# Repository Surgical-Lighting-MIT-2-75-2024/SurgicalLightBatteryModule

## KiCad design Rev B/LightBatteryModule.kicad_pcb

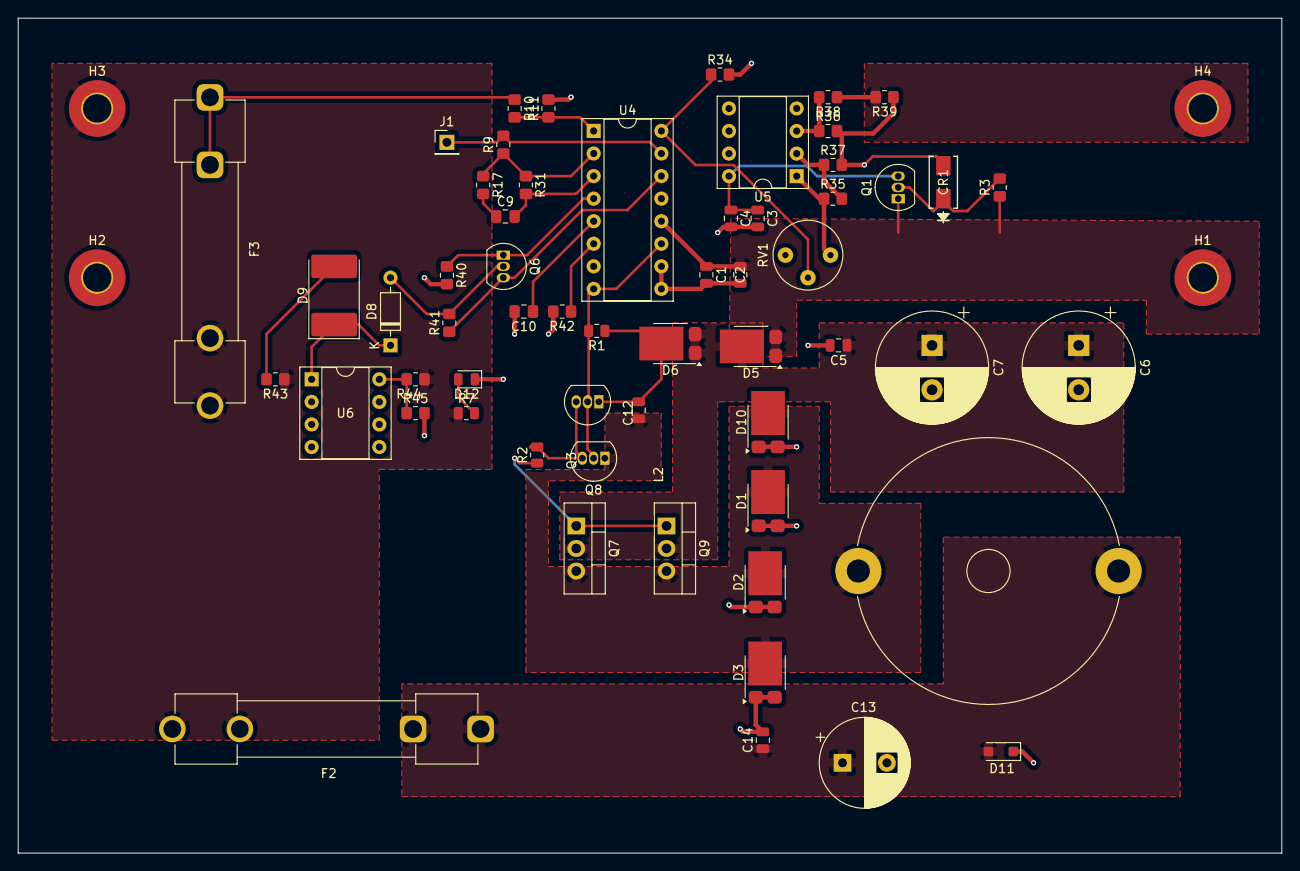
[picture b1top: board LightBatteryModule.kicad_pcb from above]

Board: 2 copper layers, 142.2 x 94.0 mm, 62 parts (0 on the bottom side), 32 nets.

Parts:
C1, C3: 1uF; C_0805_2012Metric
C2, C4, C5, C12, C14: 0.1uF; C_0805_2012Metric
C6, C7: 470uF; CP_Radial_D12.5mm_P5.00mm
C9: 100nF; C_0805_2012Metric_Pad1.18x1.45mm_HandSolder
C10: 1nF; C_0805_2012Metric_Pad1.18x1.45mm_HandSolder
C13: 22uF; CP_Radial_D10.0mm_P5.00mm
CR1: SMAZ15-13-F; SMA_DIO
D1, D2, D3, D5, D6, D10: PMEG045V150EPD; Nexperia_CFP15_SOT-1289
D8: 1N4148; D_DO-35_SOD27_P7.62mm_Horizontal
D9: LED; D_3220_8050Metric_Pad2.65x5.15mm_HandSolder
D11: SZSMF4L15CAT3G; D_SOD-123F
D12: LED Green; LED_0805_2012Metric
F2, F3: 12A; Fuseholder_Clip-6.3x32mm_Littelfuse_102071_Inline_P34.70x7.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
H1, H2, H3, H4: M3 Hole; MountingHole_3.2mm_M3_Pad_TopBottom
J1: Conn_01x01_Pin; PinHeader_1x01_P2.54mm_Vertical
L2: 100uH 10.5A; L_Radial_D29.8mm_P29.30mm_Murata_1400series
Q1: 2n3904; TO-92_Inline
Q3: BC337; TO-92_Inline
Q6: BC557; TO-92_Inline
Q7, Q9: IRLZ44N; TO-220-3_Vertical
Q8: BC327; TO-92_Inline
R1: 2k2; R_0805_2012Metric
R2: 5; R_0805_2012Metric
R3, R10, R41, R44: 10K; R_0805_2012Metric_Pad1.20x1.40mm_HandSolder
R7: 1K; R_0805_2012Metric
R9: 1K; R_0805_2012Metric_Pad1.20x1.40mm_HandSolder
R11: 2.2K; R_0805_2012Metric_Pad1.20x1.40mm_HandSolder
R17, R35, R36: 47K; R_0805_2012Metric_Pad1.20x1.40mm_HandSolder
R31: 56k; R_0805_2012Metric_Pad1.20x1.40mm_HandSolder
R34: 560R; R_0805_2012Metric_Pad1.20x1.40mm_HandSolder
R37, R38, R45: 2K; R_0805_2012Metric_Pad1.20x1.40mm_HandSolder
R39: 0R1; R_0805_2012Metric_Pad1.20x1.40mm_HandSolder
R40, R43: 2K2; R_0805_2012Metric_Pad1.20x1.40mm_HandSolder
R42: 39K; R_0805_2012Metric_Pad1.20x1.40mm_HandSolder
RV1: 10K; Potentiometer_Bourns_3339P_Vertical_HandSoldering
U4: TL494; DIP-16_W7.62mm_Socket
U5: LM358; DIP-8_W7.62mm_Socket
U6: TL431D; DIP-8_W7.62mm_Socket

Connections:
/CT: C10.1, U4.5 (CT)
/EA1+: R10.2, R11.1, U4.1 (1IN+)
/EA1-: R9.1, R17.1, R31.1, U4.2 (1IN-)
/EA2+: R34.1, RV1.2, U4.16 (2IN+)
/FB: C9.2, R31.2, U4.3 (FB)
/PWM Out: Q3.2 (B), Q8.2 (B), R1.2, U4.8 (C1), U4.11 (C2)
/RT: R42.1, U4.6 (RT)
/SOLAR 15V: C3.1, C4.1, Q1.3 (E), U5.8 (V+)
/VPOut: Q6.1 (C), R40.1, U4.4 (DTC)
/VREF: Q6.3 (E), R41.1, U4.14 (REF)
BAT+: F2.2, F3.2, H3.1, R7.1, R43.1, R44.1
BAT-: H4.1, R38.1, R39.2
GND: C1.2, C2.2, C3.2, C4.2, C5.2, C6.2, C7.2, C10.2, C13.2, C14.2, CR1.2, D1.1 (A), D1.2 (A), D2.1 (A), D2.2 (A), D3.1 (A), D3.2 (A), D10.1 (A), D10.2 (A), D11.1 (A1), D12.1 (K), H2.1, R11.2, R34.2, R36.2, R37.2, R39.1, R40.2, R42.2, R45.2, U4.7 (GND), U4.9 (E1), U4.10 (E2), U4.13 (OUTCTRL), U5.4 (V-), U6.2 (A), U6.3 (A), U6.6 (A), U6.7 (A)
MCU 2.5V: J1.1, R9.2, U4.15 (2IN-)
unnamed: C9.1, R17.2
unnamed: C12.2, D1.3 (K), D2.3 (K), D3.3 (K), D10.3 (K), L2.1, Q7.3 (S), Q8.1 (C), Q9.3 (S)
unnamed: C5.1, C6.1, C7.1, D5.3 (K), D6.1 (A), D6.2 (A), Q7.2 (D), Q9.2 (D)
unnamed: C12.1, D6.3 (K), Q3.1 (C), R1.1
unnamed: D8.2 (A), Q6.2 (B), R41.2
unnamed: D8.1 (K), D9.1 (K), U6.1 (K)
unnamed: D9.2 (A), R43.2
unnamed: C13.1, C14.1, D11.2 (A2), F2.1, L2.2
unnamed: D12.2 (A), R7.2
unnamed: F3.1, R10.1
unnamed: CR1.1, Q1.2 (B), R3.2
unnamed: Q3.3 (E), Q8.3 (E), R2.2
unnamed: Q7.1 (G), Q9.1 (G), R2.1
unnamed: R35.1, RV1.1, U5.1
unnamed: R36.1, R38.2, U5.3 (+)
unnamed: R35.2, R37.1, U5.2 (-)
unnamed: R44.2, R45.1, U6.8 (REF)
SOLAR+: C1.1, C2.1, D5.1 (A), D5.2 (A), H1.1, Q1.1 (C), R3.1, U4.12 (VCC)

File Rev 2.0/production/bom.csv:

Designator,Footprint,Quantity,Value,LCSC Part #
"C1, C3",0805,2,1uF,
C10,0805,1,1nF,
C13,CP_Radial_D10.0mm_P5.00mm,1,220uF,
C14,CP_Radial_D10.0mm_P5.00mm,1,470uF,
"C2, C4",0805,2,0.1uF,
C5,CP_Radial_D12.5mm_P5.00mm,1,220uF,
"C6, C7",CP_Radial_D12.5mm_P5.00mm,2,470uF,
C9,0805,1,100nF,
"CR1, CR2",SMA_DIO,2,SMAZ15-13-F,
"D1, D10, D2, D3, D5, D6",Nexperia_CFP15_SOT-1289,6,PMEG045V150EPD,
D11,D_SOD-123F,1,SZSMF4L15CAT3G,
D12,0805,1,LED Green,
"D4, D8",D_DO-35_SOD27_P7.62mm_Horizontal,2,1N4148,
D9,0805,1,Green Led,
F2,Fuseholder_Clip-6.3x32mm_Littelfuse_102071_Inline_P34.70x7.60mm_D2.00mm_Horizontal,1,12A,
J1,PinHeader_1x01_P2.54mm_Vertical,1,Conn_01x01_Pin,
L2,L_Radial_D29.8mm_P29.30mm_Murata_1400series,1,100uH 10.5A,
Q1,TO-92_Inline,1,2n3904,
Q2,TO-220-3_Vertical,1,IRF9540N,
Q3,TO-92_Inline,1,TIP31,
Q6,TO-92_Inline,1,2N3906,
"R1, R40, R43",0805,3,2k2,
R11,0805,1,2.2K,
"R17, R35, R36",0805,3,47K,
"R3, R41, R44",0805,3,10K,
R31,0805,1,56k,
R34,0805,1,560R,
"R37, R38, R45",0805,3,2K,
R39,0805,1,0R1,
R4,0805,1,220R,
R42,0805,1,39K,
"R7, R9",0805,2,1K,
"RV1, RV2",PinHeader_1x03_P2.54mm_Vertical,2,10K,
"TP1, TP2, TP3, TP5",TestPoint_Loop_D2.54mm_Drill1.5mm_Beaded,4,TestPoint,
U4,DIP-16_W7.62mm_Socket,1,TL494,
U5,DIP-8_W7.62mm_Socket,1,LM358,
U6,DIP-8_W7.62mm_Socket,1,TL431D,

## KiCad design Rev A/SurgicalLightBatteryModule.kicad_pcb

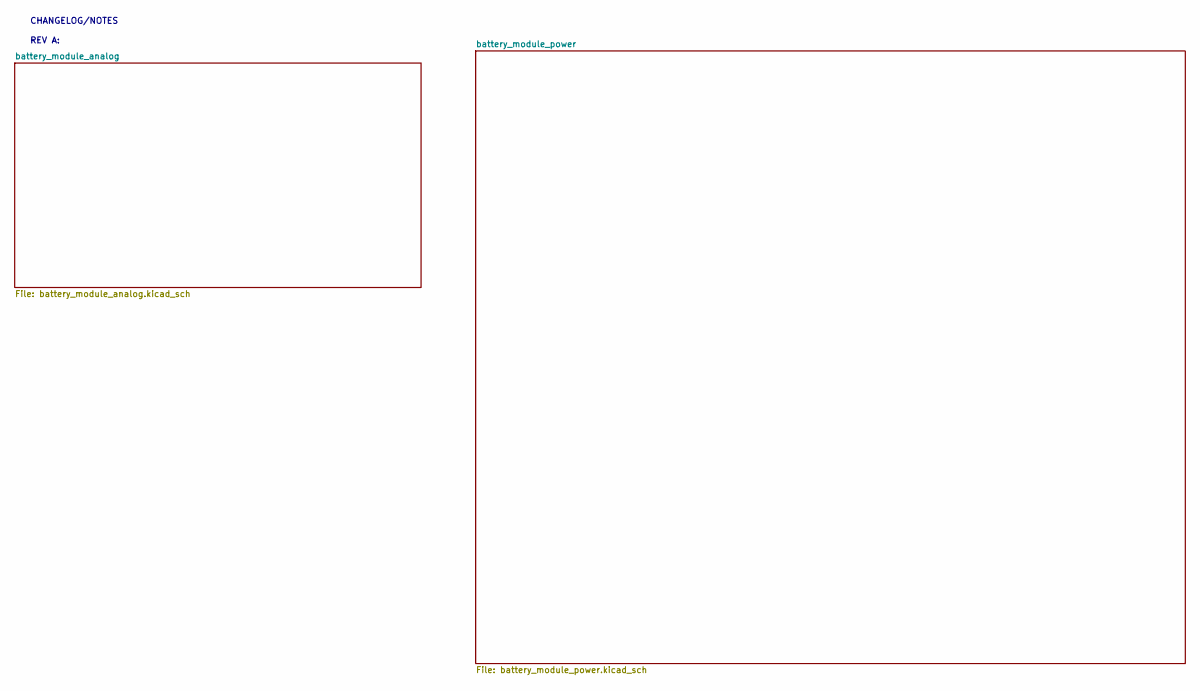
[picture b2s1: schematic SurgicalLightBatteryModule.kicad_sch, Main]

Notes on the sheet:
CHANGELOG/NOTES REV A:

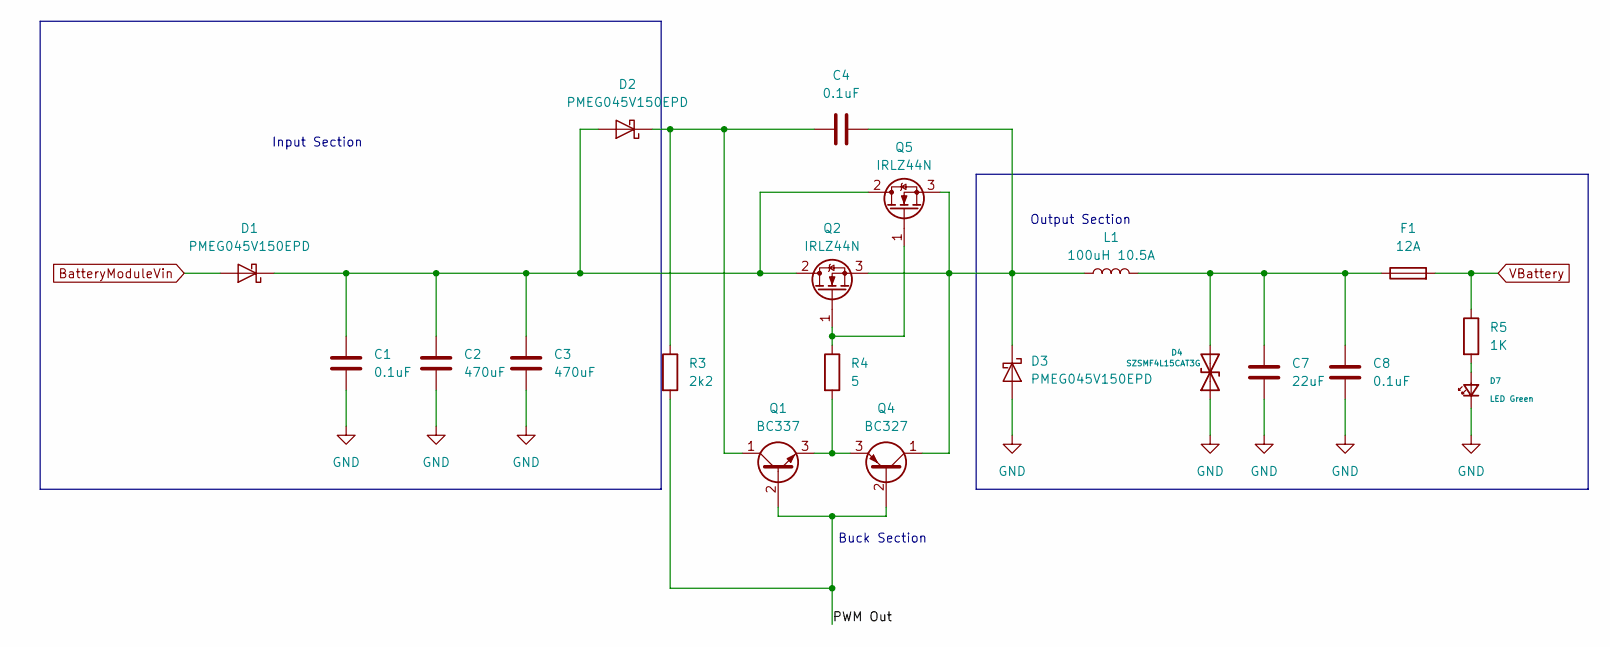
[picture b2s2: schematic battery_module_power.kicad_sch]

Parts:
C1, C4, C8: 0.1uF; C_0805_2012Metric
C2, C3: 470uF; C_0805_2012Metric_Pad1.18x1.45mm_HandSolder
C7: 22uF; C_0805_2012Metric_Pad1.18x1.45mm_HandSolder
D1, D2, D3: PMEG045V150EPD; Nexperia_CFP15_SOT-1289
D4: SZSMF4L15CAT3G; D_SOD-123F
D7: LED Green; LED_0805_2012Metric
F1: 12A; Fuse_0805_2012Metric_Pad1.15x1.40mm_HandSolder
L1: 100uH 10.5A; L_0805_2012Metric
Q1: BC337; TO-92_Inline
Q2, Q5: IRLZ44N; TO-220-3_Vertical
Q4: BC327; TO-92_Inline
R3: 2k2; R_0805_2012Metric
R4: 5; R_0805_2012Metric
R5: 1K; R_0805_2012Metric

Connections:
/battery_module_power/PWM Out: Q1.2 (B), Q4.2 (B), R3.2
BatteryModuleVin: D1.1 (A), D1.2 (A)
GND: C1.2, C2.2, C3.2, C7.2, C8.2, D3.1 (A), D3.2 (A), D4.1 (A1), D7.1 (K); also elsewhere on the board
unnamed: C1.1, C2.1, C3.1, D1.3 (K), D2.1 (A), D2.2 (A), Q2.2 (D), Q5.2 (D)
unnamed: C4.1, D2.3 (K), Q1.1 (C), R3.1
unnamed: C4.2, D3.3 (K), L1.1, Q2.3 (S), Q4.1 (C), Q5.3 (S)
unnamed: C7.1, C8.1, D4.2 (A2), F1.1, L1.2
unnamed: D7.2 (A), R5.2
unnamed: Q1.3 (E), Q4.3 (E), R4.2
unnamed: Q2.1 (G), Q5.1 (G), R4.1
VBattery: F1.2, R5.1

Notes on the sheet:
Output Section
Buck Section
Input Section

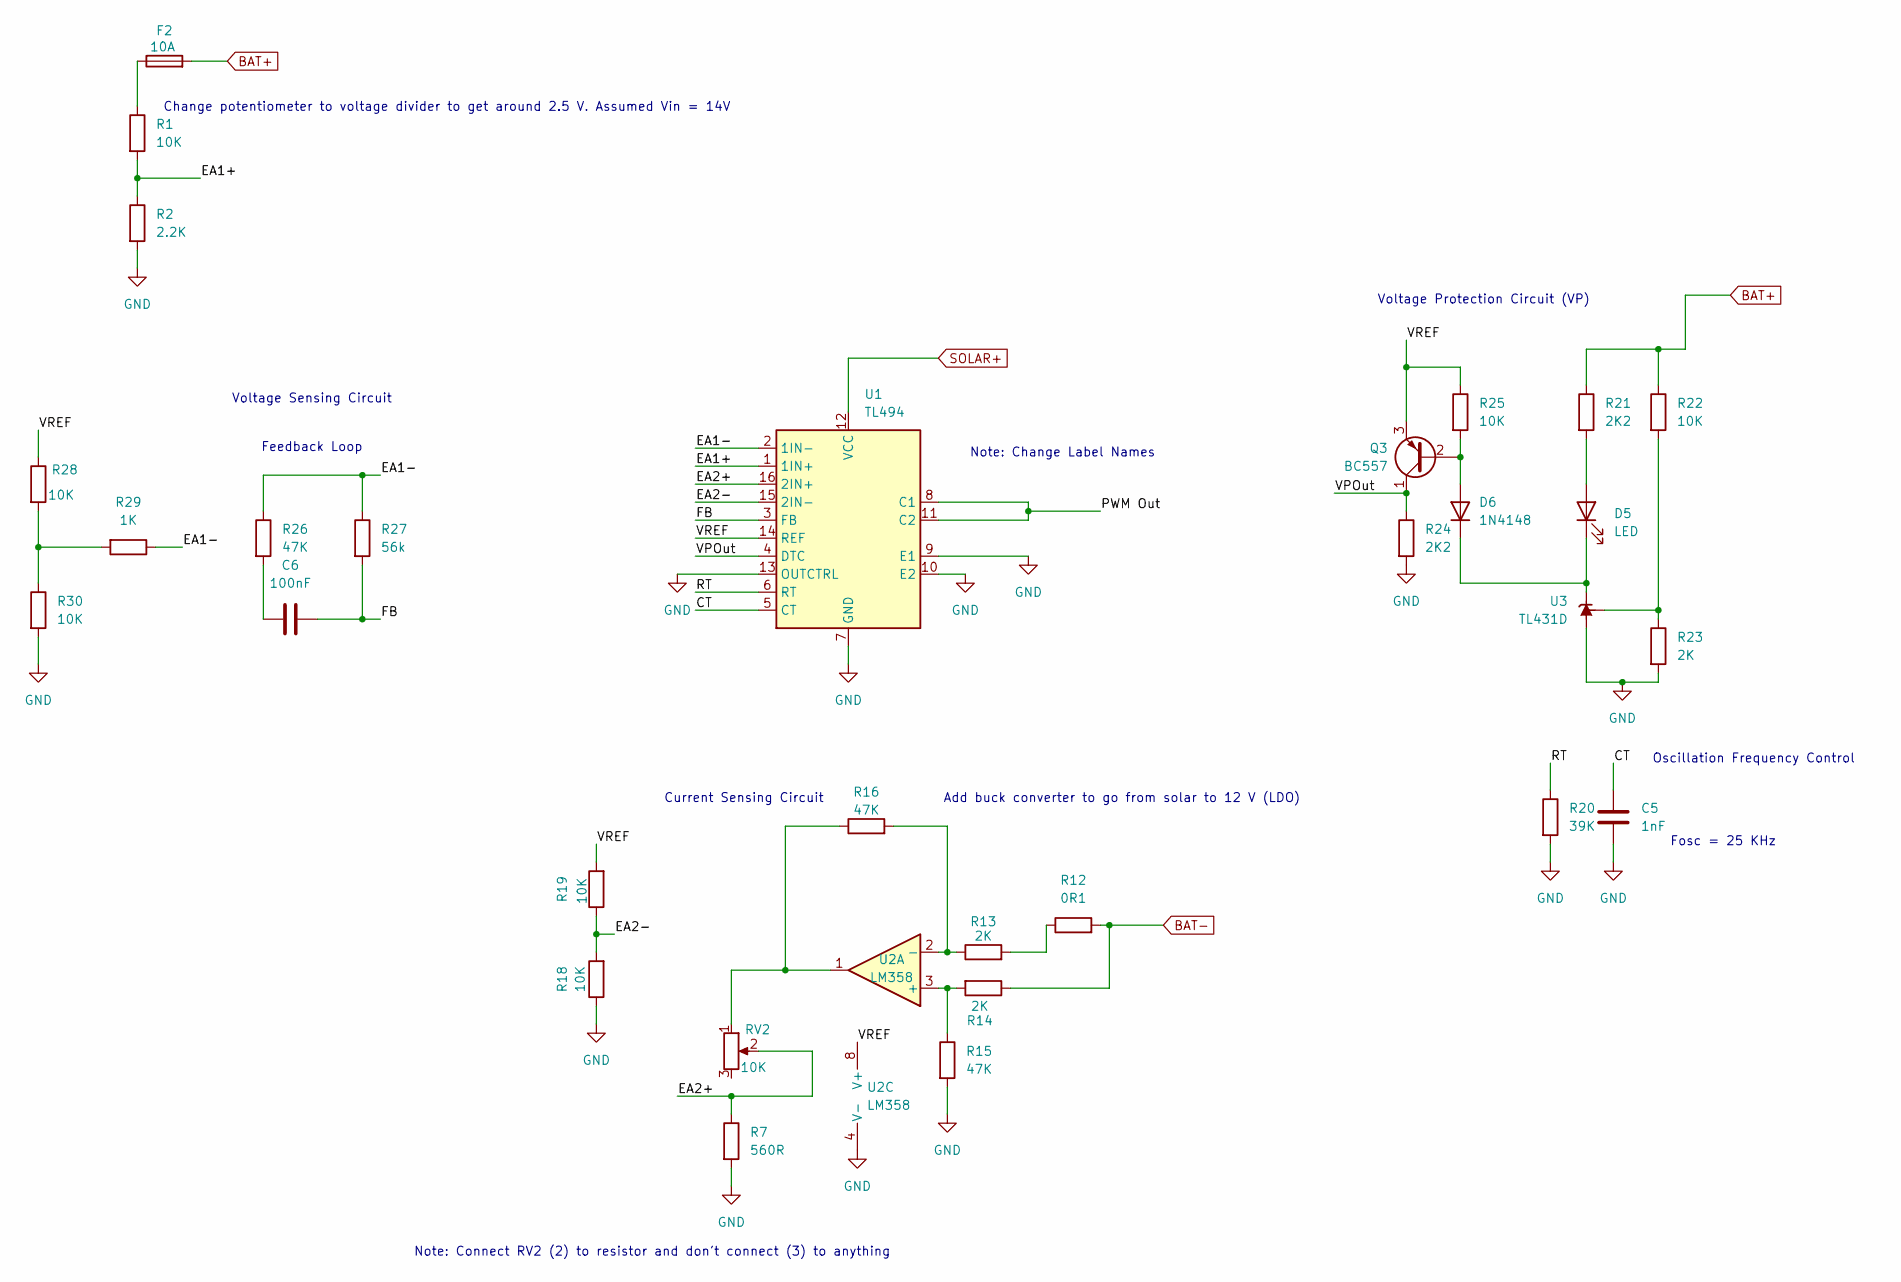
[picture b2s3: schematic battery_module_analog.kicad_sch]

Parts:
C5: 1nF; C_0805_2012Metric_Pad1.18x1.45mm_HandSolder
C6: 100nF; C_0805_2012Metric_Pad1.18x1.45mm_HandSolder
D5: LED; D_3220_8050Metric_Pad2.65x5.15mm_HandSolder
D6: 1N4148; D_DO-35_SOD27_P7.62mm_Horizontal
F2: 10A; Fuse_0805_2012Metric_Pad1.15x1.40mm_HandSolder
Q3: BC557; TO-92_Inline
R1, R18, R19, R22, R25, R28, R30: 10K; R_0805_2012Metric_Pad1.20x1.40mm_HandSolder
R2: 2.2K; R_0805_2012Metric_Pad1.20x1.40mm_HandSolder
R7: 560R; R_0805_2012Metric_Pad1.20x1.40mm_HandSolder
R12: 0R1; R_0805_2012Metric_Pad1.20x1.40mm_HandSolder
R13, R14, R23: 2K; R_0805_2012Metric_Pad1.20x1.40mm_HandSolder
R15, R16, R26: 47K; R_0805_2012Metric_Pad1.20x1.40mm_HandSolder
R20: 39K; R_0805_2012Metric_Pad1.20x1.40mm_HandSolder
R21, R24: 2K2; R_0805_2012Metric_Pad1.20x1.40mm_HandSolder
R27: 56k; R_0805_2012Metric_Pad1.20x1.40mm_HandSolder
R29: 1K; R_0805_2012Metric_Pad1.20x1.40mm_HandSolder
RV2: 10K; Potentiometer_Bourns_3339P_Vertical_HandSoldering
U1: TL494; DIP-16_W7.62mm_Socket
U2: LM358; DIP-8_W7.62mm_Socket
U3: TL431D; SOIC-8_3.9x4.9mm_P1.27mm

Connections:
/battery_module_analog/CT: C5.1, U1.5 (CT)
/battery_module_analog/EA1+: R1.2, R2.1, U1.1 (1IN+)
/battery_module_analog/EA1-: R26.1, R27.1, R29.1, U1.2 (1IN-)
/battery_module_analog/EA2+: R7.1, RV2.2, U1.16 (2IN+)
/battery_module_analog/EA2-: R18.2, R19.1, U1.15 (2IN-)
/battery_module_analog/FB: C6.2, R27.2, U1.3 (FB)
/battery_module_analog/PWM Out: U1.8 (C1), U1.11 (C2)
/battery_module_analog/RT: R20.1, U1.6 (RT)
/battery_module_analog/VPOut: Q3.1 (C), R24.1, U1.4 (DTC)
/battery_module_analog/VREF: Q3.3 (E), R19.2, R25.1, R28.1, U1.14 (REF), U2.8 (V+)
BAT+: F2.2, R21.1, R22.1
BAT-: R12.2, R14.1
GND: C5.2, R2.2, R7.2, R15.2, R18.1, R20.2, R23.2, R24.2, R30.2, U1.7 (GND), U1.9 (E1), U1.10 (E2), U1.13 (OUTCTRL), U2.4 (V-), U3.2 (A), U3.3 (A), U3.6 (A), U3.7 (A); also elsewhere on the board
unnamed: C6.1, R26.2
unnamed: D5.2 (A), R21.2
unnamed: D5.1 (K), D6.1 (K), U3.1 (K)
unnamed: D6.2 (A), Q3.2 (B), R25.2
unnamed: F2.1, R1.1
unnamed: R12.1, R13.2
unnamed: R16.1, RV2.1, U2.1
unnamed: R28.2, R29.2, R30.1
unnamed: R14.2, R15.1, U2.3 (+)
unnamed: R13.1, R16.2, U2.2 (-)
unnamed: R22.2, R23.1, U3.8 (REF)
SOLAR+: U1.12 (VCC)

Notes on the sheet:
Voltage Sensing Circuit
Change potentiometer to voltage divider to get around 2.5 V. Assumed Vin = 14V
Add buck converter to go from solar to 12 V (LDO)
Oscillation Frequency Control
Fosc = 25 KHz
Voltage Protection Circuit (VP)
Note: Connect RV2 (2) to resistor and don't connect (3) to anything
Feedback Loop
Current Sensing Circuit
Note: Change Label Names

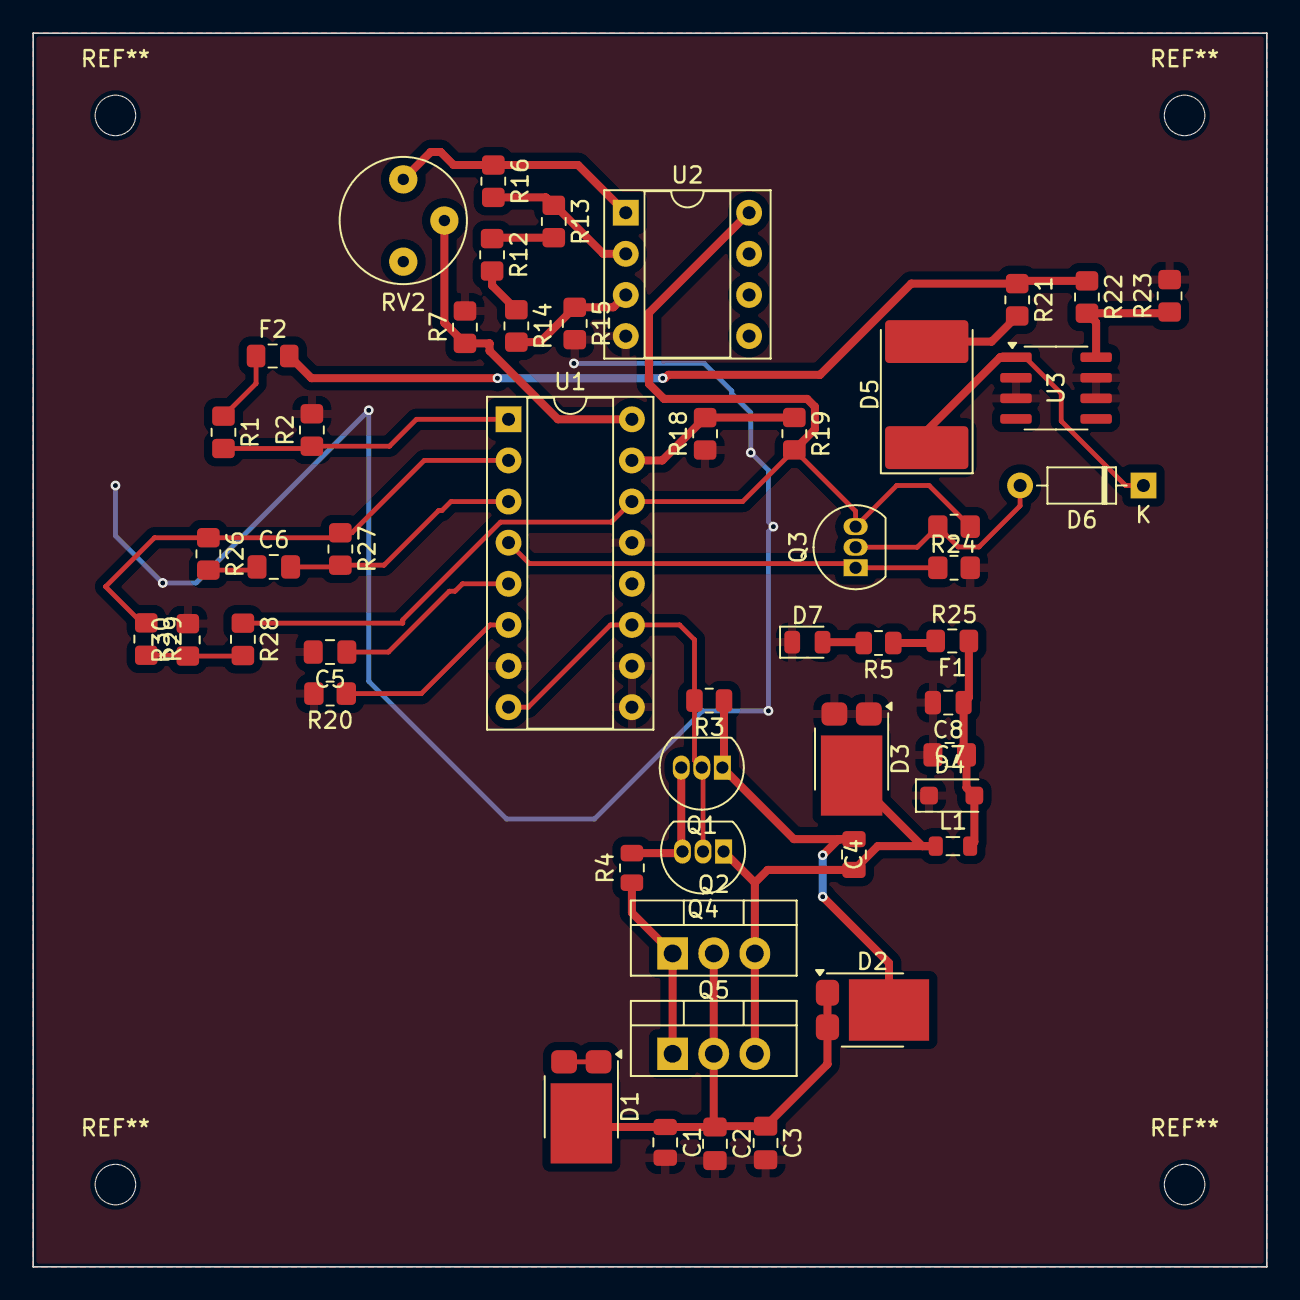
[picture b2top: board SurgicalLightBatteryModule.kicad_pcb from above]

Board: 2 copper layers, 76.2 x 76.2 mm, 51 parts (0 on the bottom side), 34 nets.

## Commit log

2024-03-21 First commit.
2024-03-21 Added .gitignore.
2024-03-24 Added buck converter schematic.
2024-03-24 Used push-pull BJT circuit to drive MOSFET.
2024-03-25 Analog MPPT
    Current sensing and voltage sensing circuits that go into the TL494 to change the PWM signal that will go into the buck converter. This schematic shows how to change the oscillation frequency of the 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
2024-03-26 Analog MPPT (Latest Update)
    Cleaned connections.
2024-03-26 Updated MPPT
2024-03-28 Updated buck.
2024-03-31 mppt schematic (03/30/2024)
    Used 5V to power up op amp. Changed configurations of potentiometers.
2024-03-31 Idk.
2024-04-01 Updated PCB and Schematics
2024-04-01 Battery Module (04/01/2024)
2024-04-03 Update 04/03/2024
2024-04-05 Update 04/05
2024-04-26 Rev 2
2024-04-26 Rev 2.0 (updated)
2024-04-27 Reverted BAT- hole position
